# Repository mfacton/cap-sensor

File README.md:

# cap-sensor
FPC variable capacitance sensing

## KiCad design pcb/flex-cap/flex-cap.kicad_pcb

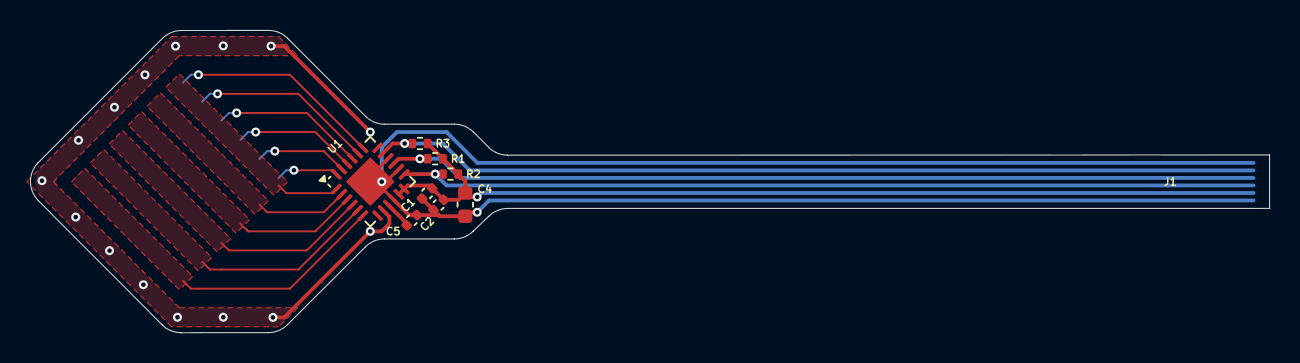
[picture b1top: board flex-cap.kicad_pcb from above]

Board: 2 copper layers, 82.4 x 20.1 mm, 9 parts (0 on the bottom side), 6 nets.

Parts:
C1: 1n; C_0402_1005Metric
C2, C5: 100n; C_0402_1005Metric
C4: 10u; C_0603_1608Metric
J1: Conn_01x06_Pin; FPC_6P_P0.5mm
R1, R2, R3: 2k2; R_0402_1005Metric
U1: AD7147-1; LFCSP-24-1EP_4x4mm_P0.5mm_EP2.3x2.3mm

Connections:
+3V3: C1.1, C2.1, C4.1, J1.5, R1.1, R2.1, R3.1, U1.11 (VCC), U1.12 (VIO)
/BIAS: C5.1, U1.9 (BIAS)
/INT: J1.2, R3.2, U1.17 (~INT)
/SCL: J1.3, R1.2, U1.15 (SCL)
/SDA: J1.4, R2.2, U1.13 (SDA)
GND: C1.2, C2.2, C4.2, C5.2, J1.1, J1.6, U1.10 (GND), U1.14 (ADD0), U1.16 (ADD1), U1.25 (PAD)

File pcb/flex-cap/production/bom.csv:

Designator,Footprint,Quantity,Value,LCSC Part #
C1,0402,1,1n,C1523
"C2, C5",0402,2,100n,C1525
C4,0603,1,10u,C19702
"R1, R2, R3",0402,3,2k2,C25879
U1,LFCSP-24-1EP_4x4mm_P0.5mm_EP2.3x2.3mm,1,AD7147-1,C207411

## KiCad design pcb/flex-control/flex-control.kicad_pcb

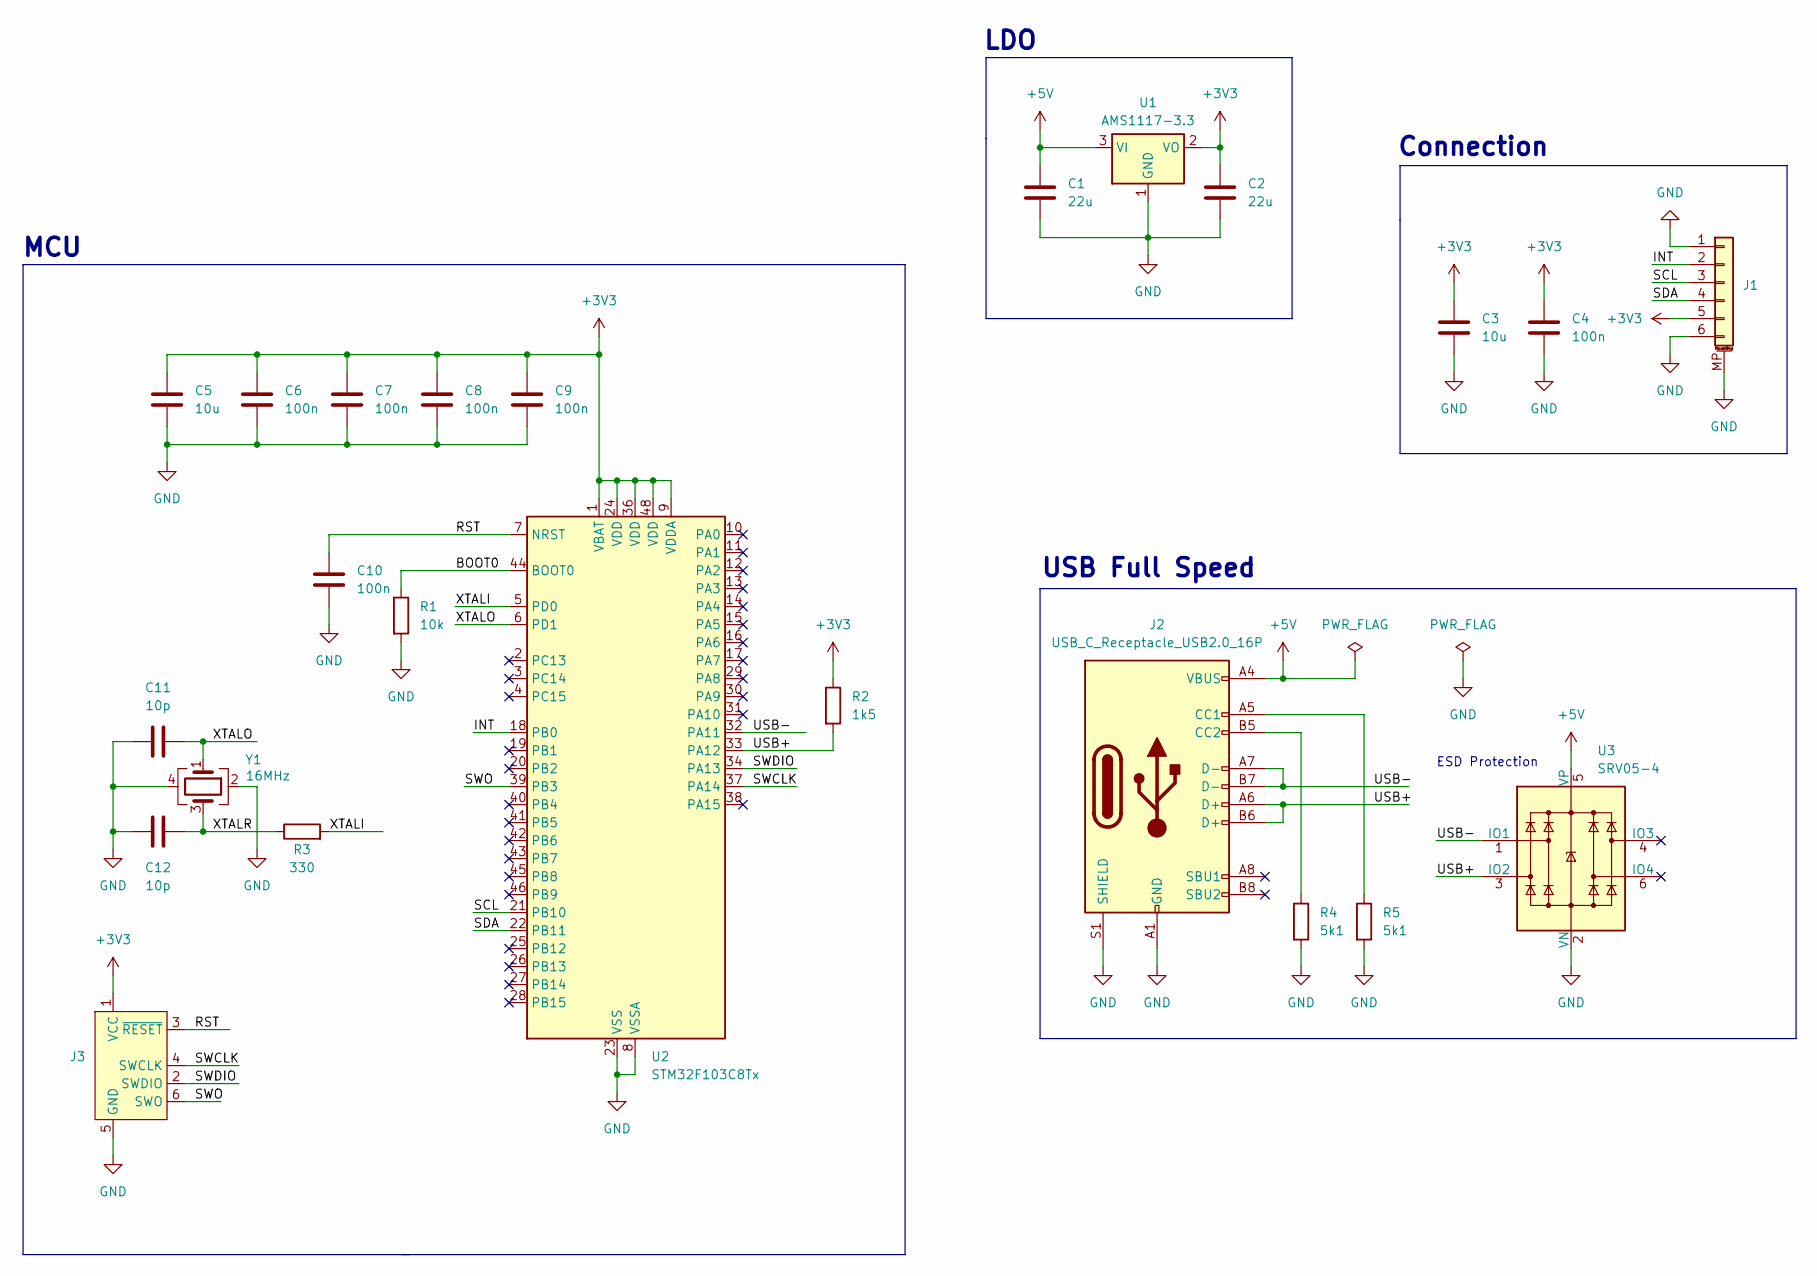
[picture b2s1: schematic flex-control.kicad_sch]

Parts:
C1: 22u; C_0805_2012Metric; LCSC C45783
C2: 22u; C_0603_1608Metric; LCSC C59461
C3, C5: 10u; C_0603_1608Metric; LCSC C19702
C4, C6, C7, C8, C9, C10: 100n; C_0402_1005Metric; LCSC C1525
C11, C12: 10p; C_0402_1005Metric; LCSC C32949
J1: Conn_01x06_MountingPin; Jushuo_AFC07-S06FCA-00_1x6-1MP_P0.50_Horizontal; LCSC C262553
J2: USB_C_Receptacle_USB2.0_16P; USB_C_Receptacle_GCT_USB4105-xx-A_16P_TopMnt_Horizontal; LCSC C165948
J3: Conn_ARM_SWD_TagConnect_TC2030-NL; Tag-Connect_TC2030-IDC-NL_2x03_P1.27mm_Vertical
R1: 10k; R_0402_1005Metric; LCSC C25744
R2: 1k5; R_0402_1005Metric; LCSC C25867
R3: 330; R_0402_1005Metric; LCSC C25104
R4, R5: 5k1; R_0402_1005Metric; LCSC C25905
U1: AMS1117-3.3; SOT-223-3_TabPin2; LCSC C6186
U2: STM32F103C8Tx; LQFP-48_7x7mm_P0.5mm; LCSC C8734
U3: SRV05-4; SOT-23-6; LCSC C7420376
Y1: 16MHz; Crystal_SMD_3225-4Pin_3.2x2.5mm; LCSC C13738

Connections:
+3V3: C2.1, C3.1, C4.1, C5.1, C6.1, C7.1, C8.1, C9.1, J1.5, J3.1 (VCC), R2.1, U1.2 (VO), U2.1 (VBAT), U2.9 (VDDA), U2.24 (VDD), U2.36 (VDD), U2.48 (VDD)
+5V: C1.1, J2.A4 (VBUS), J2.A9 (VBUS), J2.B4 (VBUS), J2.B9 (VBUS), U1.3 (VI), U3.5 (VP)
/BOOT0: R1.1, U2.44 (BOOT0)
/INT: J1.2, U2.18 (PB0)
/RST: C10.1, J3.3 (~RESET), U2.7 (NRST)
/SCL: J1.3, U2.21 (PB10)
/SDA: J1.4, U2.22 (PB11)
/SWCLK: J3.4 (SWCLK), U2.37 (PA14)
/SWDIO: J3.2 (SWDIO), U2.34 (PA13)
/SWO: J3.6 (SWO), U2.39 (PB3)
/USB+: J2.A6 (D+), J2.B6 (D+), R2.2, U2.33 (PA12), U3.3 (IO2)
/USB-: J2.A7 (D-), J2.B7 (D-), U2.32 (PA11), U3.1 (IO1)
/XTALI: R3.2, U2.5 (PD0)
/XTALO: C11.2, U2.6 (PD1), Y1.1
/XTALR: C12.2, R3.1, Y1.3
GND: C1.2, C2.2, C3.2, C4.2, C5.2, C6.2, C7.2, C8.2, C9.2, C10.2, C11.1, C12.1, J1.1, J1.6, J1.MP (MountPin), J2.A1 (GND), J2.A12 (GND), J2.B1 (GND), J2.B12 (GND), J2.S1 (SHIELD), J3.5 (GND), R1.2, R4.2, R5.2, U1.1 (GND), U2.8 (VSSA), U2.23 (VSS), U2.35 (VSS), U2.47 (VSS), U3.2 (VN), Y1.2, Y1.4
unnamed: J2.A5 (CC1), R5.1
unnamed: J2.B5 (CC2), R4.1

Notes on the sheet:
ESD Protection
MCU
Connection
LDO
USB Full Speed

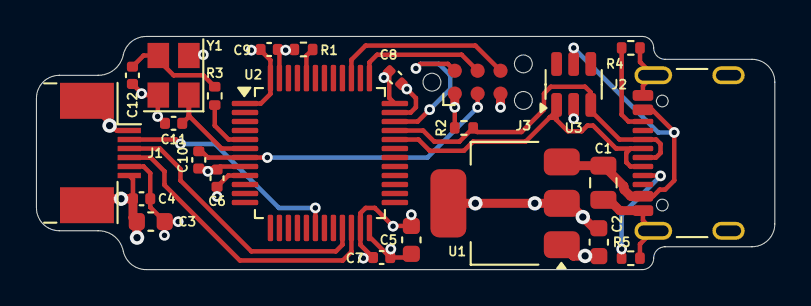
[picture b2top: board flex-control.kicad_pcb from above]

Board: 4 copper layers, 41.0 x 13.0 mm, 24 parts (0 on the bottom side), 18 nets.

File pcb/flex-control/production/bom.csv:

Designator,Footprint,Quantity,Value,LCSC Part #
C1,0805,1,22u,C45783
"C10, C4, C6, C7, C8, C9",0402,6,100n,C1525
"C11, C12",0402,2,10p,C32949
C2,0603,1,22u,C59461
"C3, C5",0603,2,10u,C19702
J1,Jushuo_AFC07-S06FCA-00_1x6-1MP_P0.50_Horizontal,1,Conn_01x06_MountingPin,C262553
J2,USB_C_Receptacle_GCT_USB4105-xx-A_16P_TopMnt_Horizontal,1,USB_C_Receptacle_USB2.0_16P,C165948
R1,0402,1,10k,C25744
R2,0402,1,1k5,C25867
R3,0402,1,330,C25104
"R4, R5",0402,2,5k1,C25905
U1,SOT-223-3_TabPin2,1,AMS1117-3.3,C6186
U2,LQFP-48_7x7mm_P0.5mm,1,STM32F103C8Tx,C8734
U3,SOT-23-6,1,SRV05-4,C7420376
Y1,Crystal_SMD_3225-4Pin_3.2x2.5mm,1,16MHz,C13738

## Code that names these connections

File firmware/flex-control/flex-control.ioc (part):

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Mcu.Name=STM32F103C(8-B)Tx
Mcu.Package=LQFP48
Mcu.UserName=STM32F103C8Tx
PA11.Mode=Device
PA11.Signal=USB_DM
PA12.Mode=Device
PA12.Signal=USB_DP
PA13.Mode=Trace_Asynchronous_SW
PA13.Signal=SYS_JTMS-SWDIO
PA14.Mode=Trace_Asynchronous_SW
PA14.Signal=SYS_JTCK-SWCLK
PB0.Signal=GPXTI0
PB10.Mode=I2C
PB10.Signal=I2C2_SCL
PB11.Mode=I2C
PB11.Signal=I2C2_SDA
PB3.Mode=Trace_Asynchronous_SW
PB3.Signal=SYS_JTDO-TRACESWO
PD0-OSC_IN.Mode=HSE-External-Oscillator
PD0-OSC_IN.Signal=RCC_OSC_IN
PD1-OSC_OUT.Mode=HSE-External-Oscillator
PD1-OSC_OUT.Signal=RCC_OSC_OUT
RCC.HSEDivPLL=RCC_HSE_PREDIV_DIV2
RCC.HSE_VALUE=16000000
RCC.SYSCLKFreq_VALUE=72000000
RCC.SYSCLKSource=RCC_SYSCLKSOURCE_PLLCLK
board=custom

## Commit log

2024-06-21 Finish flex schematic
2024-06-29 ignore kicad and stm32
2024-06-29 Finish schematic and pcb
2024-06-29 Remove lck file
2024-06-29 Setup connector in schematic
2024-06-30 Finish routing
2024-06-30 Create production files
2024-06-30 Save
2024-06-30 Make production files
2024-06-30 Setup ioc
2024-07-15 Fix pcb origins
